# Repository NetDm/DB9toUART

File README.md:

# DB9toUART

project for engraving PCB from kicad

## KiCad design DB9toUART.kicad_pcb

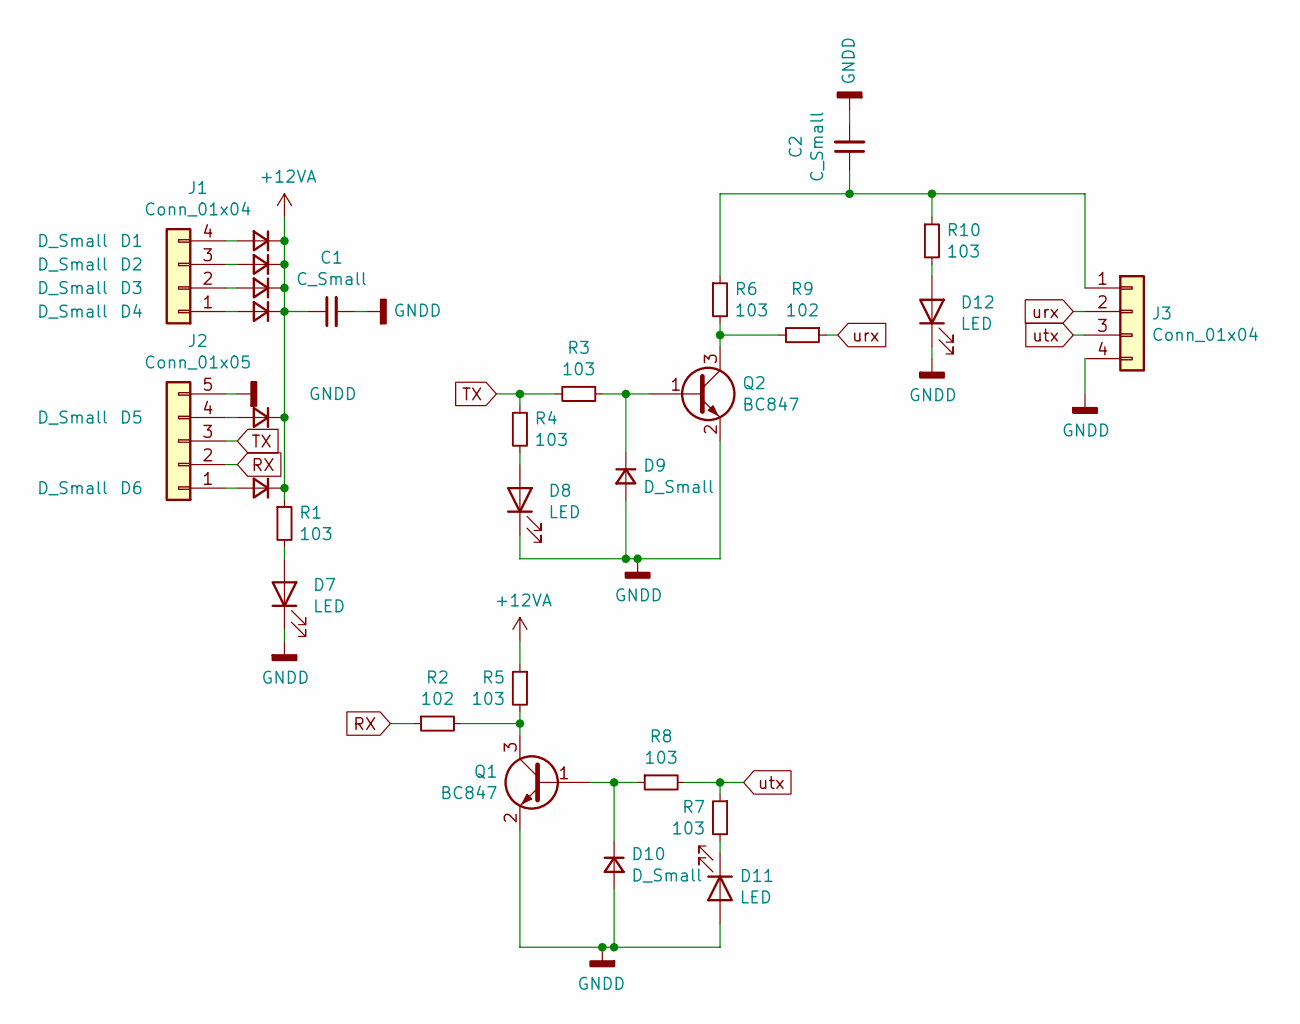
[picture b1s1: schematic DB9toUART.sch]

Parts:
C1, C2: C_Small; C_0805_2012Metric
D1, D2, D3, D4, D5, D6, D9, D10: D_Small; D_1206_3216Metric
D7, D8, D11, D12: LED; LED_0805_2012Metric
J1, J3: Conn_01x04; PinHeader_1x04_P2.54mm_Vertical
J2: Conn_01x05; PinHeader_1x05_P2.54mm_Vertical
Q1, Q2: BC847; SOT-23
R1, R3, R4, R5, R6, R7, R8, R10: 103; R_0603_1608Metric
R2, R9: 102; R_0603_1608Metric

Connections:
+12VA: C1.1, D1.1 (K), D2.1 (K), D3.1 (K), D4.1 (K), D5.1 (K), D6.1 (K), R1.1, R5.1
GNDD: C1.2, C2.2, D7.1 (K), D8.1 (K), D9.2 (A), D10.2 (A), D11.2 (A), D12.1 (K), J2.5, J3.4, Q1.2 (E), Q2.2 (E)
unnamed: C2.1, J3.1, R6.1, R10.1
unnamed: D1.2 (A), J1.4
unnamed: D2.2 (A), J1.3
unnamed: D3.2 (A), J1.2
unnamed: D4.2 (A), J1.1
unnamed: D5.2 (A), J2.4
unnamed: D6.2 (A), J2.1
unnamed: D7.2 (A), R1.2
unnamed: D8.2 (A), R4.2
unnamed: D9.1 (K), Q2.1 (B), R3.1
unnamed: D10.1 (K), Q1.1 (B), R8.1
unnamed: D11.1 (K), R7.2
unnamed: D12.2 (A), R10.2
unnamed: Q1.3 (C), R2.2, R5.2
unnamed: Q2.3 (C), R6.2, R9.2
RX: J2.2, R2.1
TX: J2.3, R3.2, R4.1
urx: J3.2, R9.1
utx: J3.3, R7.1, R8.2

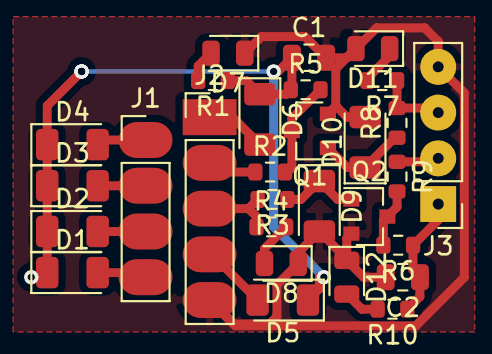
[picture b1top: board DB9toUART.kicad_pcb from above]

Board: 2 copper layers, 29 parts (0 on the bottom side), 21 nets.
